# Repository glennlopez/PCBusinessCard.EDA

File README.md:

# NFC Enabled PCB Business Card

<!--

-->

This is the ultimate business card in PCB form, designed to bridge the physical world with the digital. The front of the card has an NFC chip designed to hold enough information to store your contact info, url, email, and plain text. In the example video below, the NFC chip holds a url link to my github repository. Energy is harvested during a scan through the antenna and powers the LED. 

On the back of the card is a QR code designed to act as backup for the NFC card in case you choose to have the NFC unpopulated. The back provides written contact info for a quick visual reference, allowing you to make a quick first impression.

<b>Download the latest release [here](https://github.com/glennlopez/PCBusinessCard.EDA/releases)</b>

A good business card provides a perfect opportunity to impress a potential contact. It needs to stand out, and with this design it will not only stand out, but will also act as a phone stand. Perfect for those long airplane commutes.

## Components
- NFC chip 1kb XQFN-8 NT3H11W0FHKH
- LED SMD 0805
- 47R Resistor SMD 0603
- 220nF Capacitor SMD 0603

## NFC Antenna
NFC antenna is an open source class 4 attena design from [NXP](https://www.themobileknowledge.com/wp-content/uploads/2018/07/02-Webinar-slies-Antenna-design-for-NTAG-I2C-plus.pdf)
- Antenna loop is 2.75 uH
- Energy harvesting output VOUT is used to power the NFC chip connected to VCC pin.

## Production Samples

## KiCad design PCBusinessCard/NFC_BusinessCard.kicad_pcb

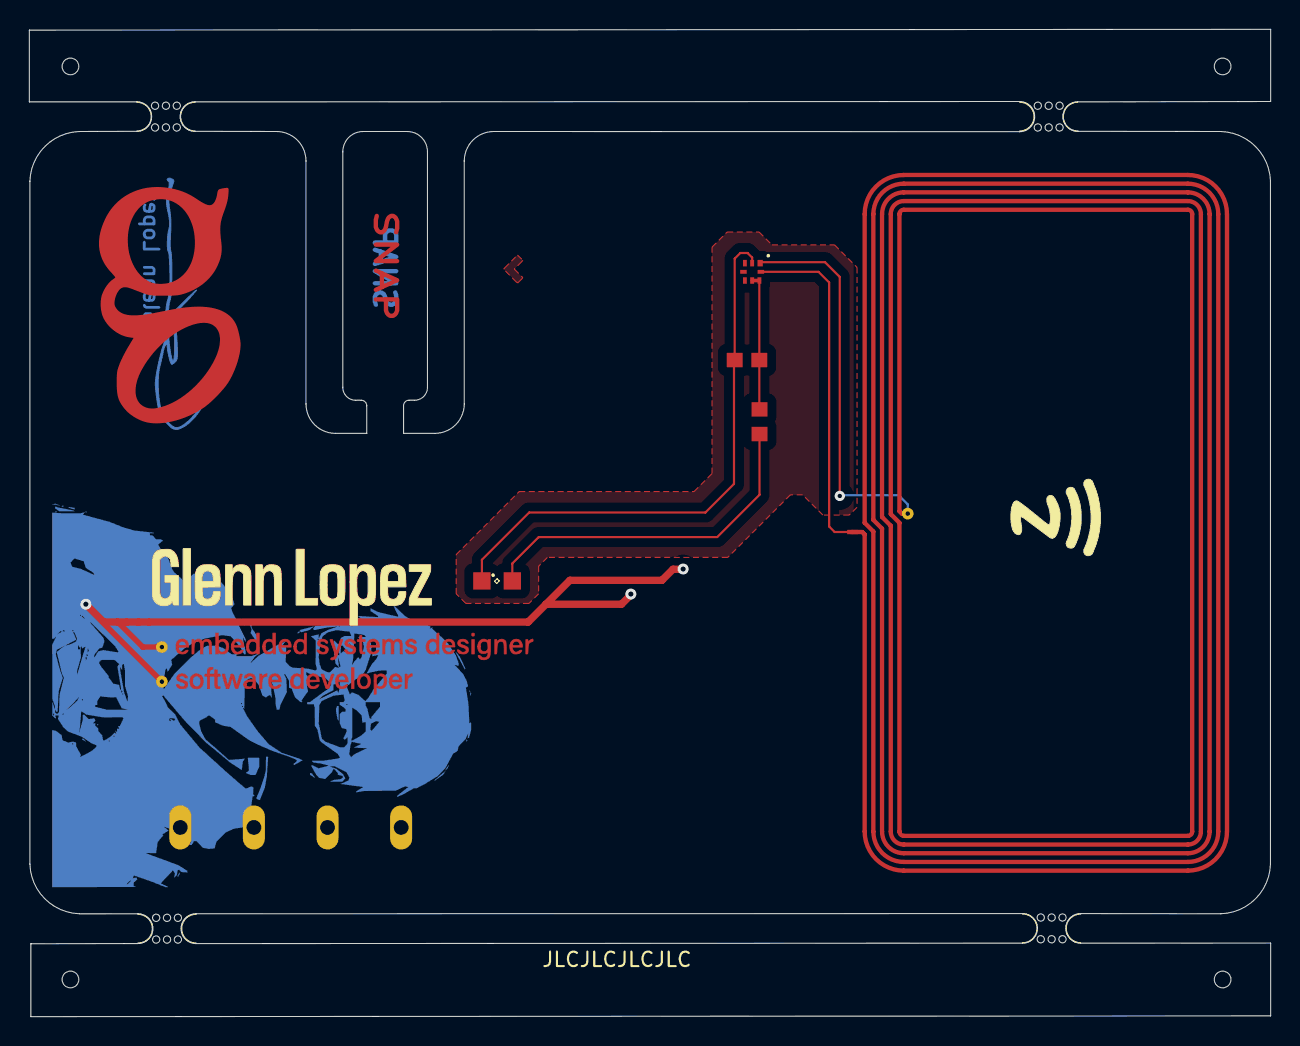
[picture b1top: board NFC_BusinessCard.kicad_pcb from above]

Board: 2 copper layers, 85.6 x 68.1 mm, 11 parts (1 on the bottom side), 5 nets.

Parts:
ANT0: 25X48MM_NFC_ANTENNA; 25X48MM_NFC
C1: 220 nf; C0603
CONTACT INFO: Contact Info; MA08-1
JLCJLCJLCJLC: Order Number JLCPCB
LED1: SML0805
NT3H1101: NT3H; XQFN8
R1: 47 Ω; R0603
mouse-bite-2mm-slot, mouse-bite-2mm-slot#2, mouse-bite-2mm-slot#3, mouse-bite-2mm-slot#4: VAL**; mouse-bite-2mm-slot

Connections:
unnamed: ANT0.P$2, NT3H1101.LA
unnamed: ANT0.P$1, NT3H1101.LB
unnamed: C1.1, NT3H1101.VCC, NT3H1101.VOUT, R1.1
unnamed: LED1.A, R1.2
unnamed: C1.2, LED1.C, NT3H1101.VSS

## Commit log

2023-01-06 Initial commit
    Added edge rails, JLCPCB order number designator, and tooling holes before adding files to repo
2023-01-06 updated gerber production files
    untested (have not sent to jlcpcb for mfg yet)
2023-01-14 added gitignore to backup folder
2023-01-14 added photos
2023-01-14 added youtube thumbnail
2023-01-14 added renders
2023-01-15 add example folder
2023-01-15 front side done
2023-01-16 finished front and back side
2023-01-16 added fiducial support to rails
2023-01-21 added more photos
2023-07-07 testing kicad 7 branch
2023-07-07 contact info changed
2023-09-28 Support for KiCad 7
2023-09-28 edited contact info
2023-09-28 backside redone
2023-09-28 removed placeholder logo
2023-09-28 added logo and fixed led

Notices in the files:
PCBusinessCard/NFC_BusinessCard.kicad_pcb:
MIT License
